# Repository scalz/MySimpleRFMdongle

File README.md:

# MySimpleRFMdongle
This is a 32bit ATSAM USB dongle with radio footprint for RFM69 or Lora Long range RFM95.

My main use is mini Serial Mysensors GW, and sniffer/debug tool with MYSController. etc.
Not a fancy thing, but I use it, and it didn't take lot of space on a panel when i ordered it so, why not :)

Tested with RFM69 and RFM95.
Just plug it, no usb cable!

Revision 1

Revision 2

Not assembled yet

###General 
------

|General spec.|  |
|---|---|---|
|Size |42.5*16.9 (mm) |
| MCU |ARM M0+ ATSAMD21E16/17/18 (same family as Arduino Zero but with 32pins) |
| Eeprom | EUI64 Eeprom |
| Authentication security | ATSHA204A chip footprint |
| Onboard led | WS2812B RGB |
| USB | USB A male connector. Sketch can be uploaded by native usb (like Arduino Zero) |
| Radio | RFM69HCW or RFM95W. SMA connector |
| Misc | Reset button |

####Onboard safety:
- Fuse + ESD protection for USB
- USB filtering

####Extension Connectors description
- Pogo pins for Cortex SWD programming
- USB for uploading sketch

####Arduino Pin description
| Arduino Pin | Description |
|---|---|---|
| 5 | Radio Interrupt Pin |
| 7 | ATSHA204A sot23 ic pin (for authentication) |
| 9 | Radio Reset Pin |
| 18 | Radio MOSI |
| 19 | Radio SCK |
| 22 | Radio MISO |
| 23 | Radio SS |
| 28 | WS2818B RGB led pin |
| 30 | SWCLK to Pogopins |
| 31 | SWDIO to Pogopins |

####Burning USB-CDC bootloader and Arduino 

I'm using Mattairtech variant board.
To find, bootloaders files and get all infos, please read : https://github.com/mattairtech/ArduinoCore-samd

Personally, I have no Atmel Ice. I use a Segger Jlink OB. It also exists cheap JTAG-SWD programmer which should work but I have not tried yet.

Simplified steps for burning bootloader with Segger Jlink OB (for more details, see links above):
1. Get a JTAG-SWD programmer. There are some cheap.
2. Download, install, and launch Atmel Studio
3. Connect your programmer to the JTAG port of the dongle
4. In Atmel Studio, go to Tools\Device Programming\ and Select your tools (the programmer), Device for MCU, Interface and apply. 
5. Try to read Id of MCU. It should be ok.
6. Then, still in the same dialog, click on Memories. Select the .hex of the bootloader you want to burn, and click Program. Then you can read, verify etc..

Then you have to install mattairtech usb driver, and boards in Arduino Ide through Boards Manager (Arduino ATSAM, and mattairtech ATSAM D21). For more details, see link above.

####Example sketch 

The example sketch is for Mysensors v2.x. This is simply the Serial GW sketch with the define for the pins. And you can add Neopixel lib.

###Overview
------

In Mysensors Serial GW mode, debugging another atsam Mysensors node. 

###Known issues
------ 

###TODO
------
- upload STL

###Donations
------

I'm trying to make opensource projects. I do this for free and sharing spirit. I don't do ads etc..
But if you think information here is worth of some money, or want to reward me, feel free to send any amount through paypal.

Or you can also order pcb here :
I will earn a little percentage that will allow me to order proto pcb and share more fun design.

Or pay me a protein smoothie if you see me! oh well, a beer is ok too :)

### Contributors
------
Always special thanks to:
- Mysensors Team for its great work
- Mattairtech, Adafruit, Sparkfun, TI, Atmel etc.. for all educational infos they share

###Links, reference and license
------
- https://www.openhardware.io/view/82/My-simple-sniffer-dongle

Copyright Scalz (2016). released under the CERN Open Hardware Licence v1.2

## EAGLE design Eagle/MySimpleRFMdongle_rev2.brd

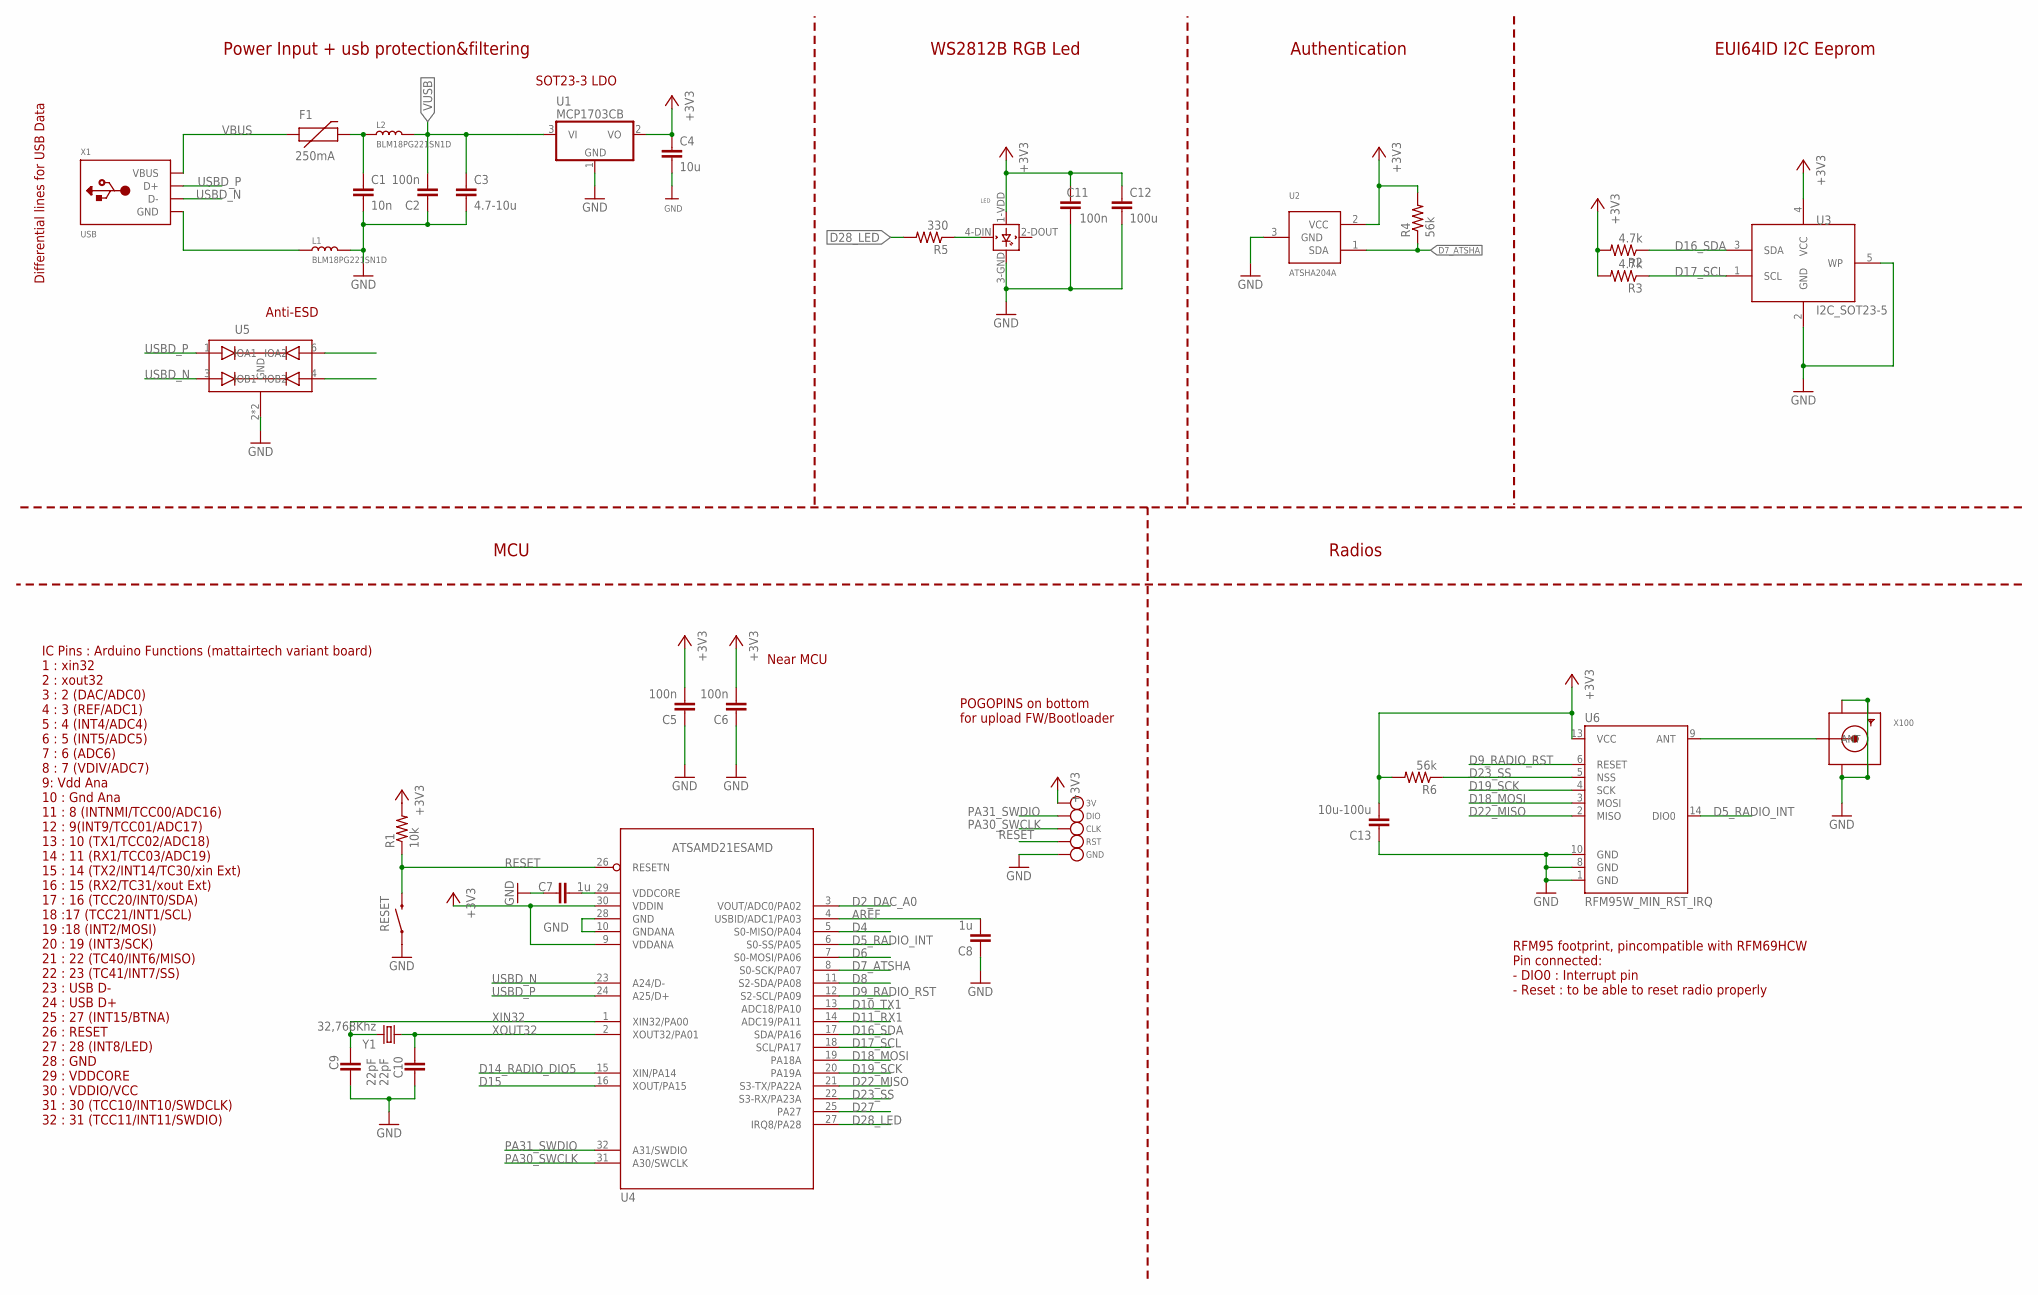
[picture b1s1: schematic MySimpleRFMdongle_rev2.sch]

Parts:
3V: TESTPOINTROUND1.5MM; TESTPOINT_ROUND_1.5MM
C1: 10n; 0603-CAP
C2, C6, C11: 100n; 0603-CAP
C3: 4.7-10u; 0805-CAP
C4: 10u; 0805-CAP
C5: 100n; 0805-CAP
C7: 1u; 0805-CAP
C8: 1u; 0603-CAP
C9, C10: 22pF; 0603-CAP
C12: 100u; 0805-CAP
C13: 10u-100u; 0805-CAP
CLK: TESTPOINTROUND1.5MM; TESTPOINT_ROUND_1.5MM
DIO: TESTPOINTROUND1.5MM; TESTPOINT_ROUND_1.5MM
F1: 250mA; PTC-1206
GND: TESTPOINTROUND1.5MM; TESTPOINT_ROUND_1.5MM
L1, L2: BLM18PG221SN1D; L0603
LED: WS2812B
R1: 10k; 0603-RES
R2, R3: 4.7k; 0603-RES
R4, R6: 56k; 0603-RES
R5: 330; 0603-RES
RESET: SWITCH-MOMENTARY-2-SMD-1101NE; TACTILE-SWITCH-1101NE
RST: TESTPOINTROUND1.5MM; TESTPOINT_ROUND_1.5MM
U1: MCP1703CB; SOT23
U2: ATSHA204A; SOT23
U3: I2C_SOT23-5; SOT-23-5
U4: ATSAMD21ESAMD; TQFP32-08
U5: TPD2E1B06
U6: RFM95W_MIN_RST_IRQ; RFM95W_MINI_RST_IRQ
X1: USB; MOLEX-48037-1000
X100: SMACONNECTOR_EDGE; SMA_EDGELAUNCH
Y1: 32,768Khz; CRYSTAL-SMD-2.0X1.2

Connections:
+3V3: 3V.P$1, C4.1, C5.2, C6.2, C11.2, C12.1, C13.2, LED.1-VDD (VDD), R1.2, R2.2, R3.2, R4.2, R6.2, U1.2 (VO), U2.2 (VCC), U3.4 (VCC), U4.9 (VDDANA), U4.30 (VDDIN), U6.13 (VCC)
AREF: C8.2, U4.4 (USBID/ADC1/PA03)
D2_DAC_A0: U4.3 (VOUT/ADC0/PA02)
D4: U4.5 (S0-MISO/PA04)
D5_RADIO_INT: U4.6 (S0-SS/PA05), U6.14 (DIO0)
D6: U4.7 (S0-MOSI/PA06)
D7_ATSHA: R4.1, U2.1 (SDA), U4.8 (S0-SCK/PA07)
D8: U4.11 (S2-SDA/PA08)
D9_RADIO_RST: U4.12 (S2-SCL/PA09), U6.6 (RESET)
D10_TX1: U4.13 (ADC18/PA10)
D11_RX1: U4.14 (ADC19/PA11)
D14_RADIO_DIO5: U4.15 (XIN/PA14)
D15: U4.16 (XOUT/PA15)
D16_SDA: R2.1, U3.3 (SDA), U4.17 (SDA/PA16)
D17_SCL: R3.1, U3.1 (SCL), U4.18 (SCL/PA17)
D18_MOSI: U4.19 (PA18A), U6.3 (MOSI)
D19_SCK: U4.20 (PA19A), U6.4 (SCK)
D22_MISO: U4.21 (S3-TX/PA22A), U6.2 (MISO)
D23_SS: R6.1, U4.22 (S3-RX/PA23A), U6.5 (NSS)
D27: U4.25 (PA27)
D28_LED: R5.2, U4.27 (IRQ8/PA28)
GND: C1.2, C2.1, C3.2, C4.2, C5.1, C6.1, C7.1, C8.1, C9.1, C10.1, C11.1, C12.2, C13.1, GND.P$1, L1.2, LED.3-GND (GND), RESET.P$1 (1), U1.1 (GND), U2.3 (GND), U3.2 (GND), U3.5 (WP), U4.10 (GNDANA), U4.28 (GND), U5.2 (GND), U5.5 (GND), U6.1 (GND), U6.8 (GND), U6.10 (GND), X100.GND@1 (GND4), X100.GND@2 (GND3), X100.GND@3 (GND2), X100.GND@4 (GND1)
unnamed: C1.1, F1.2, L2.1
unnamed: LED.4-DIN (DIN), R5.1
unnamed: U6.9 (ANT), X100.P (ANT)
PA30_SWCLK: CLK.P$1, U4.31 (A30/SWCLK)
PA31_SWDIO: DIO.P$1, U4.32 (A31/SWDIO)
RESET: R1.1, RESET.P$2 (2), RST.P$1, U4.26 (RESETN)
USBD_N: U4.23 (A24/D-), U5.3 (IOB1), U5.4 (IOB2), X1.2 (D-)
USBD_P: U4.24 (A25/D+), U5.1 (IOA1), U5.6 (IOA2), X1.3 (D+)
USBGND: L1.1, X1.4 (GND)
VBUS: F1.1, X1.1 (VBUS)
VDDCORE: C7.2, U4.29 (VDDCORE)
VUSB: C2.2, C3.1, L2.2, U1.3 (VI)
XIN32: C9.2, U4.1 (XIN32/PA00), Y1.2
XOUT32: C10.2, U4.2 (XOUT32/PA01), Y1.1

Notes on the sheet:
Radios
Authentication
RFM95 footprint, pincompatible with RFM69HCW Pin connected: - DIO0 : Interrupt pin - Reset : to be able to reset radio properly
Power Input + usb protection&filtering
WS2812B RGB Led
IC Pins : Arduino Functions (mattairtech variant board) 1 : xin32 2 : xout32 3 : 2 (DAC/ADC0) 4 : 3 (REF/ADC1) 5 : 4 (INT4/ADC4) 6 : 5 (INT5/ADC5) 7 : 6 (ADC6) 8 : 7 (VDIV/ADC7) 9: Vdd Ana 10 : Gnd Ana 11 : 8 (INTNMI/TCC00/ADC16) 12 : 9(INT9/TCC01/ADC17) 13 : 10 (TX1/TCC02/ADC18) 14 : 11 (RX1/TCC03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
Differential lines for USB Data
EUI64ID I2C Eeprom
SOT23-3 LDO
MCU
Anti-ESD
POGOPINS on bottom for upload FW/Bootloader
Near MCU

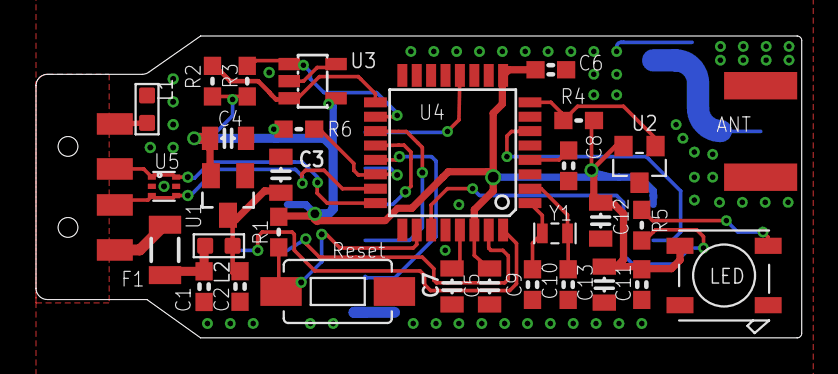
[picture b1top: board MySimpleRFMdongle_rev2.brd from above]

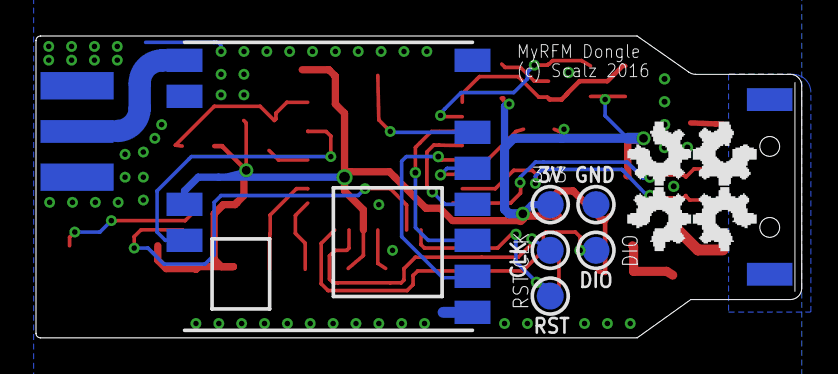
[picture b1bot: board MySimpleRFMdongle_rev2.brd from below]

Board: 2 copper layers, 42.5 x 16.8 mm, 39 parts (7 on the bottom side), 27 nets.

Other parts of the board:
U$2: OPENHW_SMALL_OSHPARK

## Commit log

2016-12-04 update description
2016-12-04 update description and design files

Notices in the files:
parts and their libraries:
SparkFun-FreqCtrl: Licensing: Creative Commons ShareAlike 4.0 International - https://creativecommons.org/licenses/by-sa/4.0
microbuilder: This work is placed in the public domain, and may be freely used for commercial and non-commercial work with the following conditions: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
